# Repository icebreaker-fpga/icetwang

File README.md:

The iCEBreaker-Bitsy FPGA based 1D LED game system.

This project has moved to [Codeberg](https://codeberg.org/icebreaker-fpga/icetwang).

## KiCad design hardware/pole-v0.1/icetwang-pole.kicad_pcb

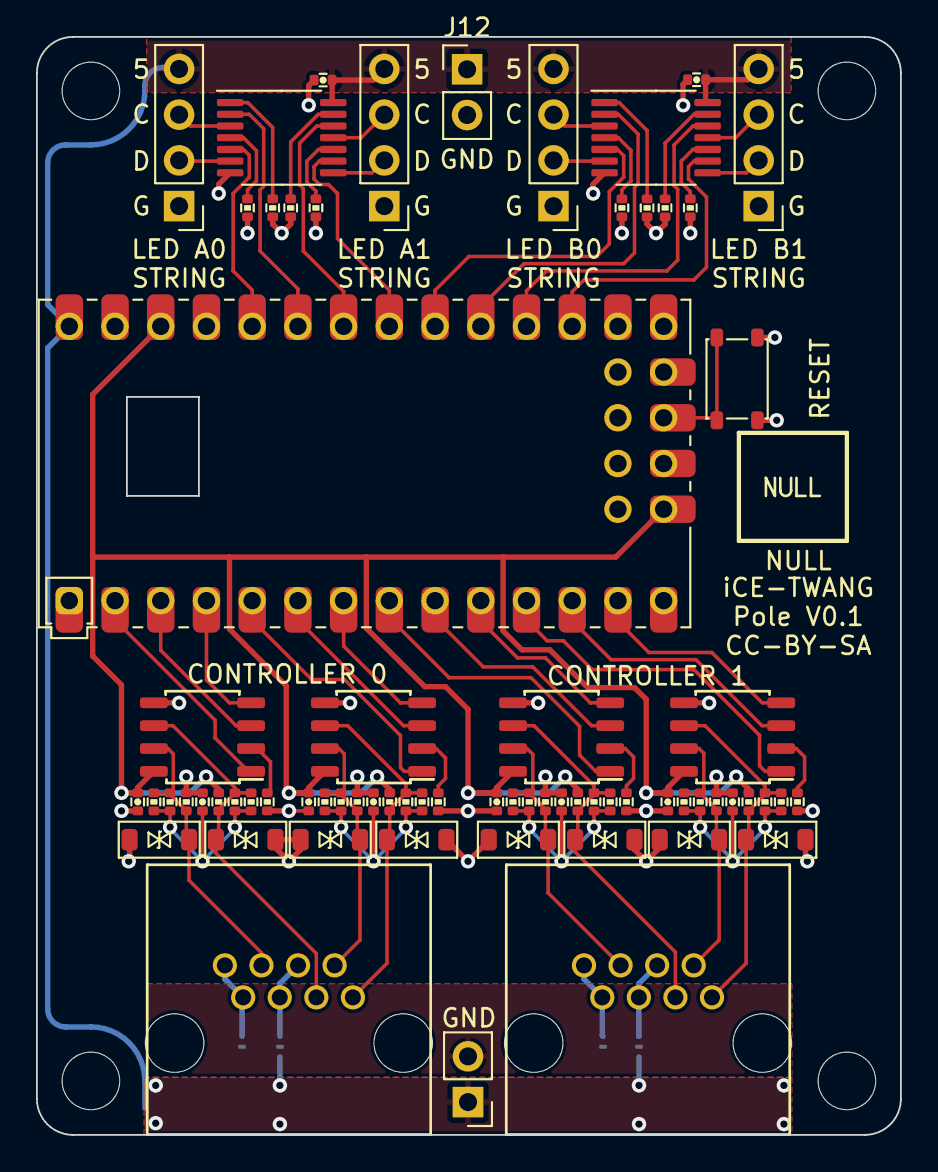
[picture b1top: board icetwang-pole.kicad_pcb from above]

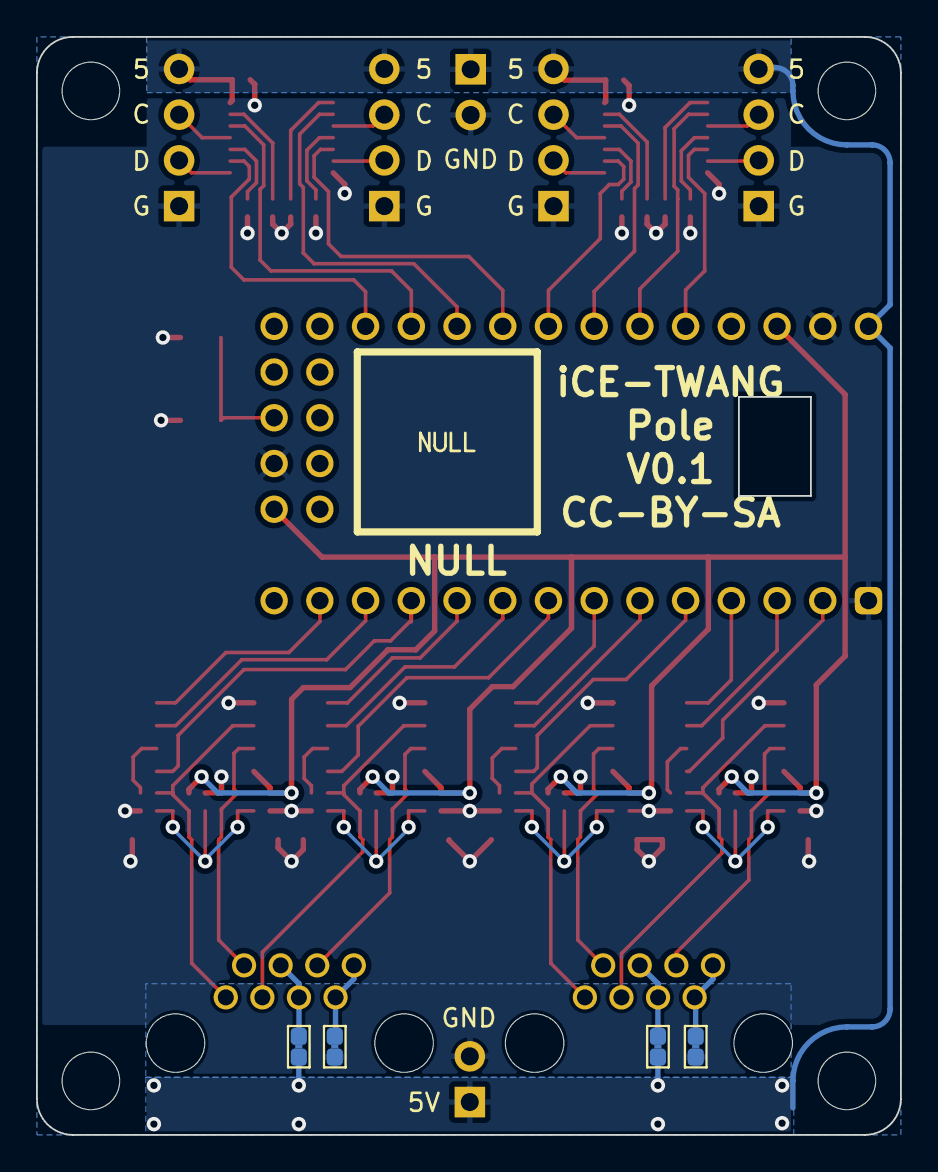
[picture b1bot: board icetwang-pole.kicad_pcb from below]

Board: 2 copper layers, 48.0 x 61.0 mm, 74 parts (4 on the bottom side), 60 nets.

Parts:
A1: iCEBreaker_Bitsy
C1, C2, C3, C4, C5, C6, C7, C8, C9, C10: 100n; C_0402
J1, J4: COMM5V; J_NC_0603_40
J2, J5: COMMGND; J_NC_0603_40
J3, J6: RJ45; AMPHENOL_RJHSE5080
J7, J8, J9, J10: RGB_LED; PinHeader_1x04_P2.54mm_Vertical
J11, J12: 5V; PinHeader_1x02_P2.54mm_Vertical
R1, R2, R15, R16, R29, R30, R31, R32, R33, R34, R35, R36: 10k; R_0402
R3, R4, R5, R6, R8, R9, R12, R13, R17, R18, R19, R20, R22, R23, R26, R27: 118R; R_0402
R7, R10, R11, R14, R21, R24, R25, R28: 620R; R_0402
SW1: TACT; SW_SPST_3x4x2.5
TVS1, TVS2, TVS3, TVS4, TVS5, TVS6, TVS7, TVS8: SMF15CA; D_SOD-123-TVS-BIDI
U1, U2, U3, U4: SN65HVD75; SOIC-8_5x4mm_Pitch1.27mm
U5, U6: 74AHCT125; TSSOP-14_4.4x5mm_P0.65mm

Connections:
+3V3: A1.26 (3V3), A1.29 (3V3), C1.1, C2.1, C5.1, C6.1, R7.1, R11.1, R21.1, R25.1, U1.8 (VCC), U2.8 (VCC), U3.8 (VCC), U4.8 (VCC)
+5V: A1.28 (VIN), C9.1, C10.1, J1.2, J4.2, J7.4, J8.4, J9.4, J10.4, J11.1, J12.1, U5.14 (VCC), U6.14 (VCC)
/CTRL0_CLK_DE: A1.3 (P1), U2.3 (DE)
/CTRL0_CLK_RX: A1.2 (P0), U2.1 (R)
/CTRL0_CLK_TX: A1.4 (P2), U2.4 (D)
/CTRL0_DAT_DE: A1.6 (P4), U1.3 (DE)
/CTRL0_DAT_RX: A1.5 (P3), U1.1 (R)
/CTRL0_DAT_TX: A1.7 (P5), U1.4 (D)
/CTRL1_CLK_DE: A1.9 (P7), U4.3 (DE)
/CTRL1_CLK_RX: A1.8 (P6), U4.1 (R)
/CTRL1_CLK_TX: A1.10 (P8), U4.4 (D)
/CTRL1_DAT_DE: A1.12 (P10), U3.3 (DE)
/CTRL1_DAT_RX: A1.11 (P9), U3.1 (R)
/CTRL1_DAT_TX: A1.13 (P11), U3.4 (D)
/LEDa0_CLK: A1.23 (P21), U5.2
/LEDa0_DAT: A1.24 (P22), U5.5
/LEDa1_CLK: A1.22 (P20), U5.12
/LEDa1_DAT: A1.21 (P19), U5.9
/LEDa/CLK0x: J7.3, U5.3
/LEDa/CLK1x: J8.3, U5.11
/LEDa/DAT0x: J7.2, U5.6
/LEDa/DAT1x: J8.2, U5.8
/LEDb0_CLK: A1.19 (P17), U6.2
/LEDb0_DAT: A1.20 (P18), U6.5
/LEDb1_CLK: A1.18 (P16), U6.12
/LEDb1_DAT: A1.17 (P15), U6.9
/LEDb/CLK0x: J9.3, U6.3
/LEDb/CLK1x: J10.3, U6.11
/LEDb/DAT0x: J9.2, U6.6
/LEDb/DAT1x: J10.2, U6.8
/comm0/CLK_N: J3.6, R6.1, R13.1, R14.1, TVS4.1 (A1), U2.7 (~B)
/comm0/CLK_P: J3.3, R5.1, R11.2, R12.1, TVS3.2 (A2), U2.6 (A)
/comm0/CLK_~RE: R2.1, U2.2 (~RE)
/comm0/COMM5V: J1.1, J3.4, J3.5
/comm0/COMMGND: J2.2, J3.7, J3.8
/comm0/DAT_N: J3.2, R4.1, R9.1, R10.1, TVS2.1 (A1), U1.7 (~B)
/comm0/DAT_P: J3.1, R3.1, R7.2, R8.1, TVS1.2 (A2), U1.6 (A)
/comm0/DAT_~RE: R1.1, U1.2 (~RE)
/comm1/CLK_N: J6.6, R20.1, R27.1, R28.1, TVS8.1 (A1), U4.7 (~B)
/comm1/CLK_P: J6.3, R19.1, R25.2, R26.1, TVS7.2 (A2), U4.6 (A)
/comm1/CLK_~RE: R16.1, U4.2 (~RE)
/comm1/COMM5V: J4.1, J6.4, J6.5
/comm1/COMMGND: J5.2, J6.7, J6.8
/comm1/DAT_N: J6.2, R18.1, R23.1, R24.1, TVS6.1 (A1), U3.7 (~B)
/comm1/DAT_P: J6.1, R17.1, R21.2, R22.1, TVS5.2 (A2), U3.6 (A)
/comm1/DAT_~RE: R15.1, U3.2 (~RE)
GND: A1.1 (GND), A1.27 (GND), A1.30 (GND), C1.2, C2.2, C3.1, C4.1, C5.2, C6.2, C7.1, C8.1, C9.2, C10.2, J2.1, J5.1, J7.1, J8.1, J9.1, J10.1, J11.2, J12.2, R1.2, R2.2, R10.2, R14.2, R15.2, R16.2, R24.2, R28.2, R29.2, R30.2, R31.2, R32.2, R33.2, R34.2, R35.2, R36.2, SW1.2, TVS1.1 (A1), TVS2.2 (A2), TVS3.1 (A1), TVS4.2 (A2), TVS5.1 (A1), TVS6.2 (A2), TVS7.1 (A1), TVS8.2 (A2), U1.5 (GND), U2.5 (GND), U3.5 (GND), U4.5 (GND), U5.7 (GND), U6.7 (GND)
unnamed: A1.31 (CRESET), SW1.1
unnamed: C3.2, R3.2, R4.2, R8.2, R9.2
unnamed: C4.2, R5.2, R6.2, R12.2, R13.2
unnamed: C7.2, R17.2, R18.2, R22.2, R23.2
unnamed: C8.2, R19.2, R20.2, R26.2, R27.2
unnamed: R29.1, U5.1
unnamed: R30.1, U5.4
unnamed: R31.1, U5.13
unnamed: R32.1, U5.10
unnamed: R33.1, U6.1
unnamed: R34.1, U6.4
unnamed: R35.1, U6.13
unnamed: R36.1, U6.10

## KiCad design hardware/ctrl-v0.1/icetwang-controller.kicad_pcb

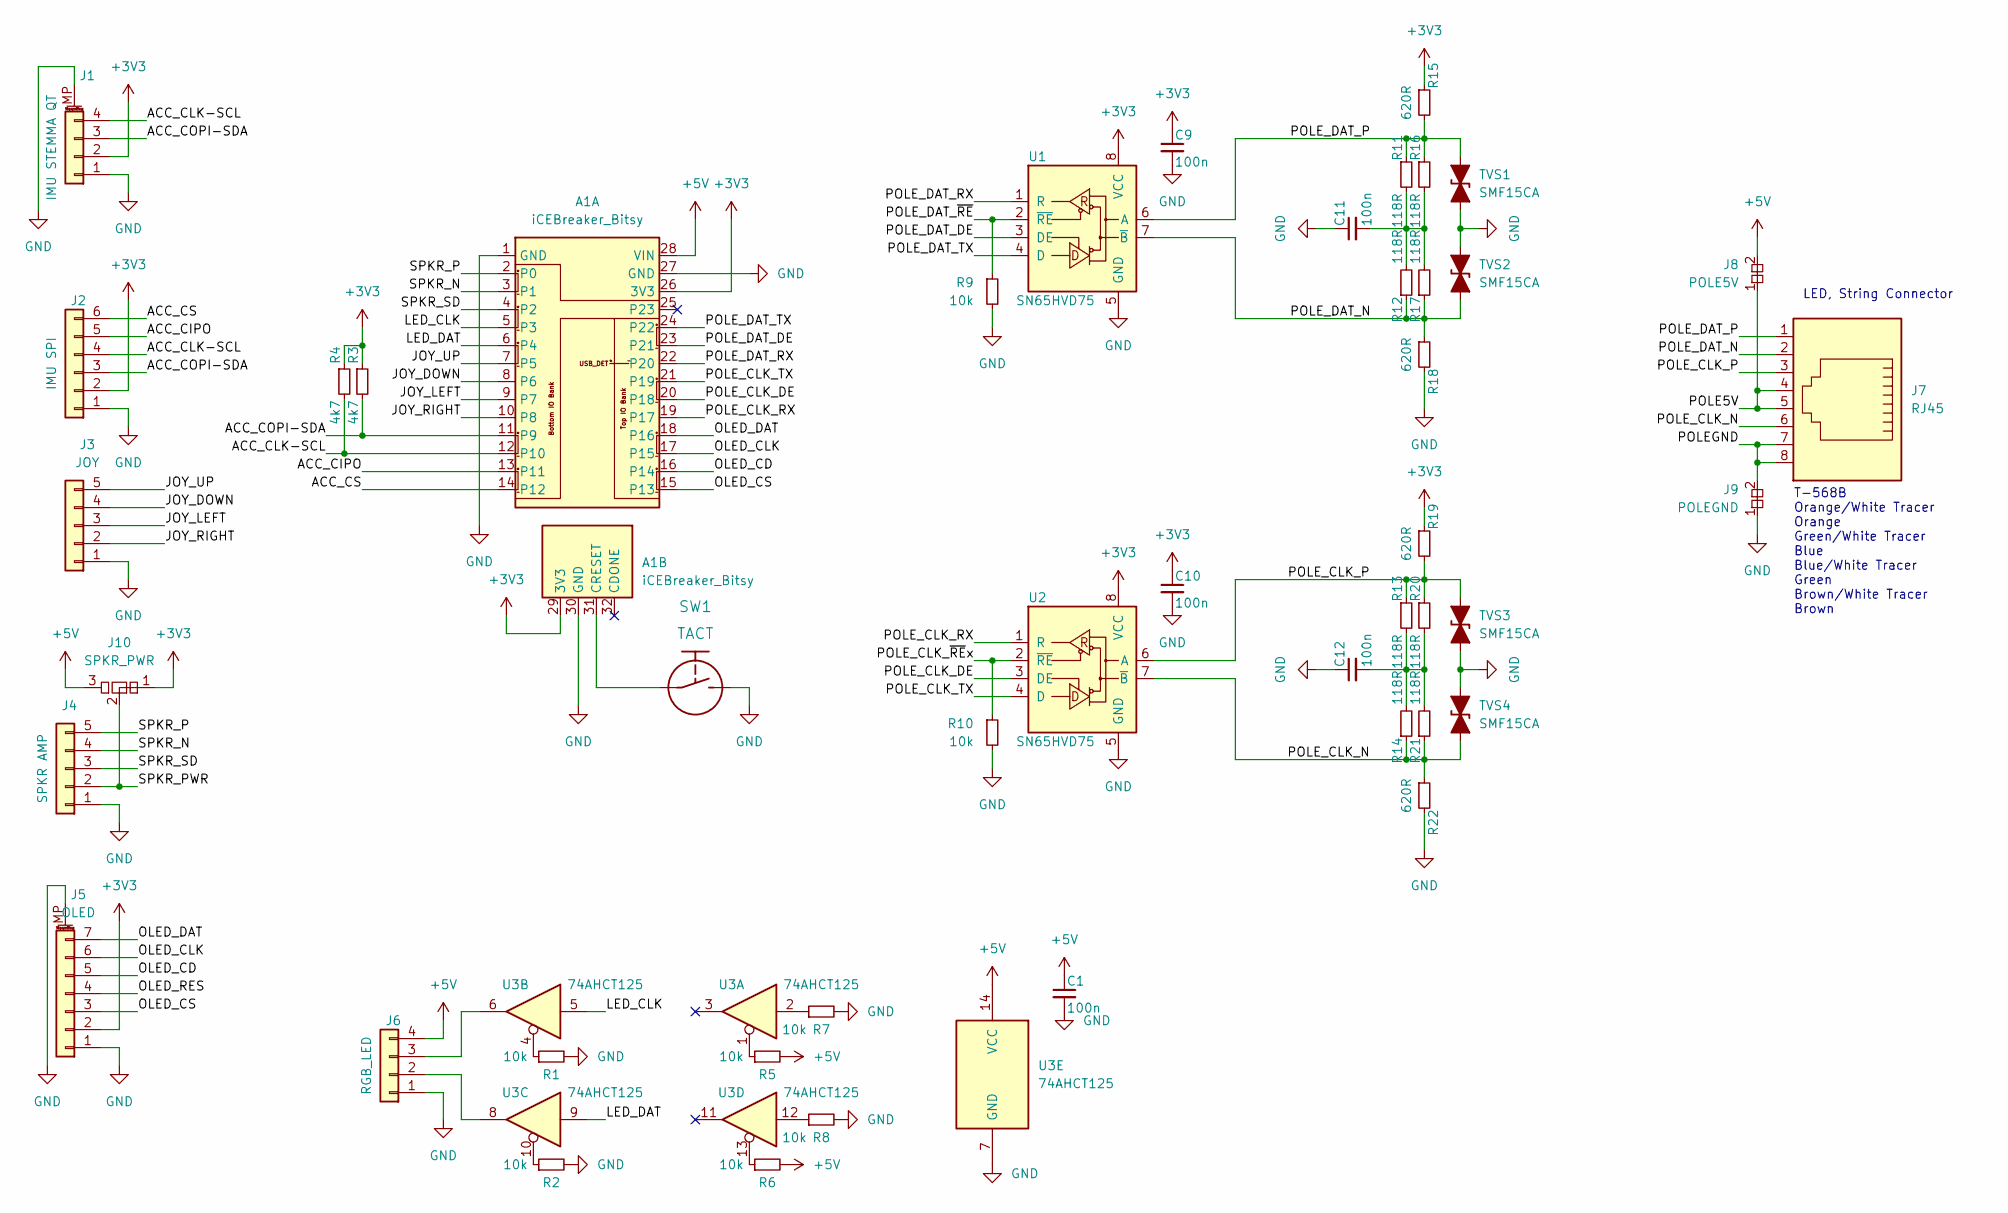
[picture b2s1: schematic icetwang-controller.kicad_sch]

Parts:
A1: iCEBreaker_Bitsy
C1, C9, C10, C11, C12: 100n; C_0402
J1: IMU STEMMA QT; JST_SH_SM04B-SRSS-TB_1x04-1MP_P1.00mm_Horizontal
J2: IMU SPI; PinHeader_1x06_P2.54mm_Vertical
J3: JOY; PinHeader_1x05_P2.54mm_Vertical
J4: SPKR AMP; PinHeader_1x05_P2.54mm_Vertical
J5: OLED; Molex_PicoBlade_53261-0771_1x07-1MP_P1.25mm_Horizontal
J6: RGB_LED; PinHeader_1x04_P2.54mm_Vertical
J7: RJ45; AMPHENOL_RJHSE5080
J8: POLE5V; J_NC_0603_40
J9: POLEGND; J_NC_0603_40
J10: SPKR_PWR; J_NCNO_0903_30
R1, R2, R5, R6, R7, R8, R9, R10: 10k; R_0402
R3, R4: 4k7; R_0402
R11, R12, R13, R14, R16, R17, R20, R21: 118R; R_0402
R15, R18, R19, R22: 620R; R_0402
SW1: TACT; SW_SPST_3x4x2.5
TVS1, TVS2, TVS3, TVS4: SMF15CA; D_SOD-123-TVS-BIDI
U1, U2: SN65HVD75; SOIC-8_5x4mm_Pitch1.27mm
U3: 74AHCT125; TSSOP-14_4.4x5mm_P0.65mm

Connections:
+3V3: A1.26 (3V3), A1.29 (3V3), C9.1, C10.1, J1.2, J2.2, J5.2, J10.1, R3.1, R4.1, R15.1, R19.1, U1.8 (VCC), U2.8 (VCC)
+5V: A1.28 (VIN), C1.1, J6.4, J8.2, J10.3, R5.2, R6.2, U3.14 (VCC)
/ACC_CIPO: A1.13 (P11), J2.5
/ACC_CLK-SCL: A1.12 (P10), J1.4, J2.4, R4.2
/ACC_COPI-SDA: A1.11 (P9), J1.3, J2.3, R3.2
/ACC_CS: A1.14 (P12), J2.6
/JOY_DOWN: A1.8 (P6), J3.4
/JOY_LEFT: A1.9 (P7), J3.3
/JOY_RIGHT: A1.10 (P8), J3.2
/JOY_UP: A1.7 (P5), J3.5
/LED_CLK: A1.5 (P3), U3.5
/LED_DAT: A1.6 (P4), U3.9
/OLED_CD: A1.16 (P14), J5.5
/OLED_CLK: A1.17 (P15), J5.6
/OLED_CS: A1.15 (P13), J5.3
/OLED_DAT: A1.18 (P16), J5.7
/OLED_RES: J5.4
/POLE5V: J7.4, J7.5, J8.1
/POLEGND: J7.7, J7.8, J9.2
/POLE_CLK_DE: A1.20 (P18), U2.3 (DE)
/POLE_CLK_N: J7.6, R14.1, R21.1, R22.1, TVS4.1 (A1), U2.7 (~B)
/POLE_CLK_P: J7.3, R13.1, R19.2, R20.1, TVS3.2 (A2), U2.6 (A)
/POLE_CLK_RX: A1.19 (P17), U2.1 (R)
/POLE_CLK_TX: A1.21 (P19), U2.4 (D)
/POLE_CLK_~REx: R10.1, U2.2 (~RE)
/POLE_DAT_DE: A1.23 (P21), U1.3 (DE)
/POLE_DAT_N: J7.2, R12.1, R17.1, R18.1, TVS2.1 (A1), U1.7 (~B)
/POLE_DAT_P: J7.1, R11.1, R15.2, R16.1, TVS1.2 (A2), U1.6 (A)
/POLE_DAT_RX: A1.22 (P20), U1.1 (R)
/POLE_DAT_TX: A1.24 (P22), U1.4 (D)
/POLE_DAT_~RE: R9.1, U1.2 (~RE)
/SPKR_N: A1.3 (P1), J4.4
/SPKR_P: A1.2 (P0), J4.5
/SPKR_PWR: J4.2, J10.2
/SPKR_SD: A1.4 (P2), J4.3
GND: A1.1 (GND), A1.27 (GND), A1.30 (GND), C1.2, C9.2, C10.2, C11.1, C12.1, J1.1, J1.MP (MountPin), J2.1, J3.1, J4.1, J5.1, J5.MP (MountPin), J6.1, J9.1, R1.2, R2.2, R7.2, R8.2, R9.2, R10.2, R18.2, R22.2, SW1.2, TVS1.1 (A1), TVS2.2 (A2), TVS3.1 (A1), TVS4.2 (A2), U1.5 (GND), U2.5 (GND), U3.7 (GND)
unnamed: A1.31 (CRESET), SW1.1
unnamed: C11.2, R11.2, R12.2, R16.2, R17.2
unnamed: C12.2, R13.2, R14.2, R20.2, R21.2
unnamed: R1.1, U3.4
unnamed: R2.1, U3.10
unnamed: R5.1, U3.1
unnamed: R6.1, U3.13
unnamed: R7.1, U3.2
unnamed: R8.1, U3.12
unnamed: J6.3, U3.6
unnamed: J6.2, U3.8

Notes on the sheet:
T-568B Orange/White Tracer Orange Green/White Tracer Blue Blue/White Tracer Green Brown/White Tracer Brown
LED, String Connector

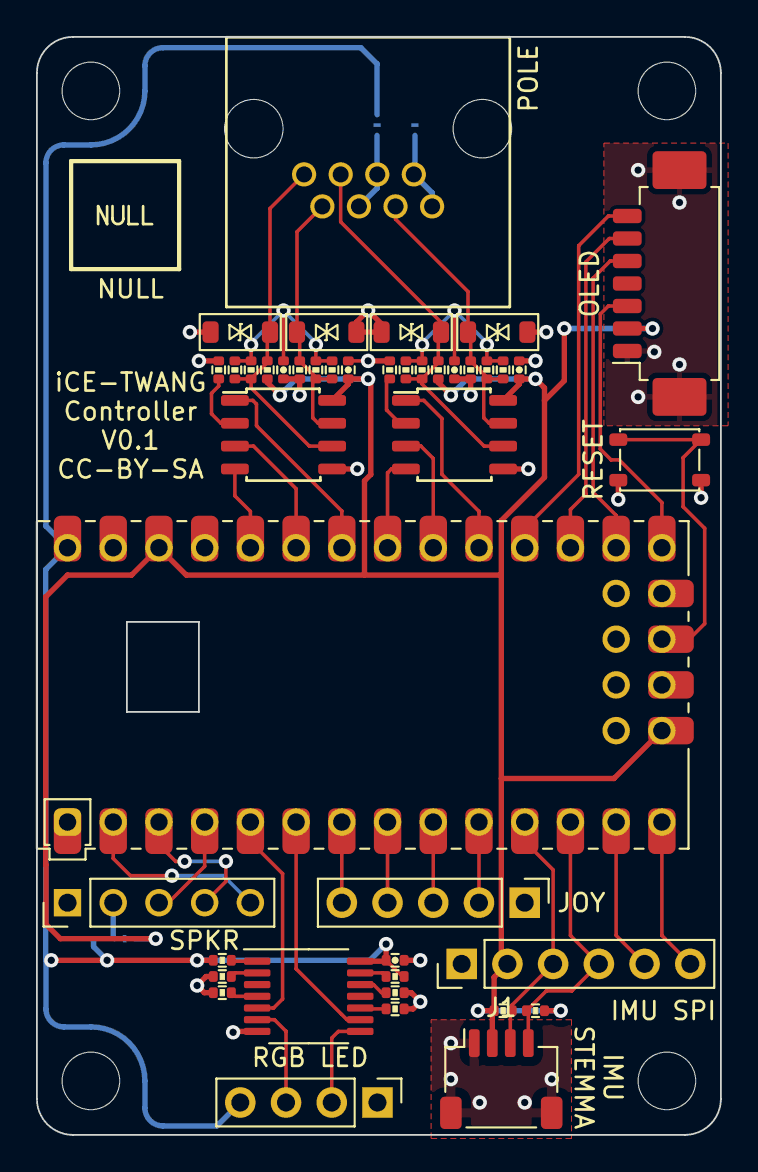
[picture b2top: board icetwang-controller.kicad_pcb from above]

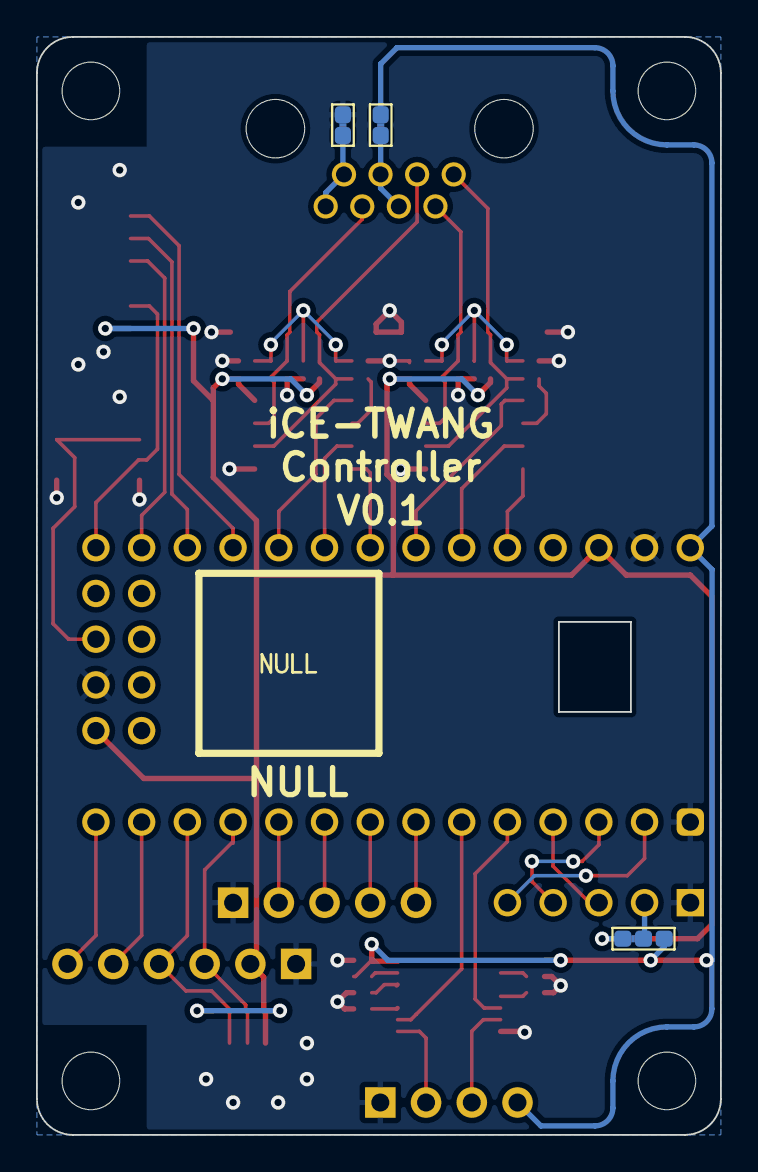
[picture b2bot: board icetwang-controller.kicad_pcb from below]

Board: 2 copper layers, 38.0 x 61.0 mm, 46 parts (3 on the bottom side), 46 nets.

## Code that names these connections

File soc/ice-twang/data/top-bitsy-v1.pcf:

# SPI
set_io -nowarn spi_mosi 14
set_io -nowarn spi_miso 17
set_io -nowarn spi_clk 15
set_io -nowarn spi_flash_cs_n 16
set_io -nowarn spi_ram_cs_n 6

# USB
set_io -nowarn usb_dp 42
set_io -nowarn usb_dn 38
set_io -nowarn usb_pu 37

# UART
set_io -nowarn uart_rx 47
set_io -nowarn uart_tx 44

# Clock
set_io -nowarn clk_in 35

# Button
set_io -nowarn btn 2

# Leds
set_io -nowarn rgb[0] 39
set_io -nowarn rgb[1] 40
set_io -nowarn rgb[2] 41
set_io -nowarn led    25 # P13

# LED String
set_io -nowarn ls_clk  45
set_io -nowarn ls_data  4

# Arcade Joystick
set_io -nowarn joy_up    3  # P5
set_io -nowarn joy_down  9  # P6
set_io -nowarn joy_left  10 # P7
set_io -nowarn joy_right 11 # P8

# I2C
set_io -nowarn i2c_sda   12 # P9
set_io -nowarn i2c_scl   21 # P10

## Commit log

2021-10-05 Initial commit of the ctrl and pole PCB designs.
2021-10-11 Initial commit of the icetwang soc, and a Rust blinky program.
2021-10-11 Added top level README.md
2021-10-11 fix #![no_std] can't find crate for test in vscode.
2021-10-11 Updated PKL.
2021-10-11 Swapped to NULL logos and added pdf schematics.
2021-10-17 Implemented print macro using UART.
2021-10-18 Minor module use fix.
2021-10-18 Initial commit of the lowest level APA102 LED protocol generator.
    This includes a testbench to excercise the generator.
2021-10-18 Output the test bench testpattern on the hardware.
2021-10-27 Removed apa102 test output runner duplicate from tb.
2021-10-27 SB_IO can be simulated so no need to disable it in simulation.
2021-10-27 First draft of the ledstring wishbone interface with framebuffer.
2021-10-27 Initial test code to excercise the ledstring framebuffer interface.
2021-10-27 Added some more things to .gitignore
2021-10-30 Initial LED string FB with Rust control.
2021-10-31 Added timer hardware. Fixed register offset issue in Rust.
    Now we are able to use a hardware timer to keep framerate.
2021-10-31 Added arcade joystick hardware and test firmware.
2021-10-31 Correted the bit count in the register padding.
2021-10-31 Fixed joystick decoding. Improved debug output.
2021-11-01 Initial commit of the dungeon game.
    Mostly a copy of the blinky code.
2021-11-01 Renamed the hardware ledstring interface to hal.
    Also changed the led data format to be compatible with the rtwang code.
2021-11-01 Got some of the basic rTWANG code working.
2021-11-02 Added sin using lut.
2021-11-02 Output time for debug.
2021-11-02 Moved virtual led string inside twang.
    Also the virtual string is now 1000 LED long and mapped to the physical
    size.
2021-11-02 Got the attractmode/screensaver to work.
2021-11-02 Added timeout to enter attract mode.
2021-11-02 Enemy spawning and levels.
2021-11-03 Added spawners.
2021-11-03 Added and updated missing license headers.
2021-11-03 Added lava.
    Need to improve our rand implementation to make it look right.
2021-11-03 Added conveyors.
2021-11-03 Minor cleanup.
2021-11-03 Disable debug output.
2021-11-04 Added top level state machine and startup animation.
2021-11-05 Rotate the playfield
2021-11-10 Add glob brightness const and add 240 str settings
2021-11-11 Add a panic handler.
    The new panic handler prints the panic information to the serial debug
    console.
2021-11-11 Fixed some minor variable wrapping bugs.
2021-11-11 Made the use of our embedded print optional.
    Preparing to add simulated version of the game.
2021-11-11 Added desktop simulated icetwang-dungeon.
2021-11-12 Modified drawing to use the raw LED data directly.
    This saves a lot of computation as one does not have to map from the
    virtual string to the real one with every pixel write. Also we only use
    as much CPU as we really need to. We still might run out of frame time
    when using really long LED strings, but not having to do the mapping
    calculation for every pixel will not happen on every LED so it will
    still be better.
2021-11-12 Fixed startup animation.
2021-11-12 Debug output clears the rest of the line to mitigate artifacts.
2021-11-12 Added the FastLED random8 implementation.
    Replaced my even less good pseudo random algorithm in screensaver with
    the "new" one.
2021-11-12 Added startup animation sparkle.
2021-11-12 Added randomness ot the lava animation.
2021-11-12 Made the enemies unaffected by the conveyor belts.
2021-11-12 Added all remaining levels except end boss.
    Also added a way to set attack with, needed for level 16.
2021-11-12 Fixed enemy/player side calculation.
    Enemies that spawend behind the player had the wrong side set.
    Also fixed level 8, the spawner was sending the enemies in the wrong
    direction.
2021-11-13 Added first half of the death animation.
    Still missing the particles.
2021-11-13 Added death particles.
2021-11-13 Corrected some overflow panics.
2021-11-13 Added player lives, display and reset to begining when out of lives.
2021-11-13 Keep default lives after dying in level 0.
2021-11-15 Added game over animation.
2021-11-15 Updated READMEs a bit.
2021-11-16 Added some pictures to the main README.
2021-11-18 Refactored the main game state machine to carry more of the state variables.
    Level and screensaver timeout were class variables. Now they are
    carried along with the game states that handle them.
2021-11-18 Removed an unnecessary self import.
2021-11-18 Panic if we try to build an invalid level.
2021-11-18 Implemented Boss entity and level. closes #6, closes #13
2021-11-18 Renamed Screensaver to Attract. closes #15
2021-11-18 Removed state stage repetition in loopback state transitions.
2021-11-18 Added Win animation. closes #14
2021-11-18 Added BossKilled animation. closes #33
2021-11-20 Added license headers to the blink firmware.
2021-11-30 Initial commit and test of i2c peripheral and IMU read.
2021-12-01 Ported i2c driver to use embedded-hal.
2021-12-08 Make timer not run when en is not set.
2021-12-08 Added timer testbench
2021-12-08 Added blocking delay traits to timer.
2021-12-08 Enable divider in test bench to expose en strobe bug.
2021-12-08 Added panic handler to the blink test firmware.
2021-12-08 Fixed timer bug. `prev_en` was not resetting when disabling the timer.
2021-12-08 Cleaned up. Now reading out the IMU works using the sensor crate.
2026-05-24 We have moved to Codeberg see README.

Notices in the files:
hardware/ctrl-v0.1/icetwang-controller.kicad_pcb:
CC-BY-SA
hardware/pole-v0.1/icetwang-pole.kicad_pcb:
(C) 2021 1BitSquared
(C) 2021 Piotr Esden-Tempski
License: CC-BY-SA 4.0
